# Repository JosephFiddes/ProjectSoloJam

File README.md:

# ProjectSoloJam (Work In Progress)
 Files and info for my solo jam project.

Physical controller to send commands to REAPER, via Open Sound Control. The controller can toggle recording, change track volumes, and set record arming for tracks.

A template REAPER project set up for the controller is found under SoloJamTemplate/SoloJamTemplate.rpp.

## Assembly
Solder the electronic components to the PCB. Note the Arduino UNO is connected via header pins.

Place four of Corner Washer Thing 1 on the piece of wood, and then place the PCB on top, such that the washers are going through the PCB's four corner holes (note: the top-left corner hole is underneath the Arduino UNO - see the image above).

Nail the PCB to the wood piece using nails with a 3mm diameter.

(optional) Place Corner Washer Thing 2 on each of the nails.

## Setup
### Dependencies
Currently, the solution is only designed for Windows.

The following dependencies are required:
 - [oscpp](https://github.com/kaoskorobase/oscpp): library for constructing and parsing OpenSoundControl packets.
 - windows.h

### Compilation

#### Serial2OSC

Prior to compilation, make sure that the port being used by the Arduino matches to port used by Serial2OSC. This can be done by opening serial2osc.cpp, finding the line `#define SERIAL_PORT "COM7"` and changing the `"COM7"` to whatever port the Arduino is using.

This project makes use of the winsock2.h library, and is compiled with MinGW (`g++`). Run `build` to compile the program.

#### Controller
The code for the controller is run on an Arduino UNO, and can be compiled in the Arduino IDE. The electrical circuit diagram of the controller is shown below:

A higher quality version of the image above may be found by [clicking here](./Controller/Controller%20PCB%20Files/Controller%20Schematic.pdf).

### Required REAPER Settings
REAPER needs to have OSC control enabled. 

1. Go to Preferences -> Control/OSC/Web. 
2. Add "OSC (Open Sound Control)" Control surface, with mode "Local port"
3. Set Local listen port to `2345`.

## Operation

With REAPER open, run serial2osc.exe. Pressing a button activates record arm for the corresponding track, and deactivates the record arm for the previous track.

## Bill of Materials

| Product | Qty  |
| ------- | ---: |
| **Electronic Components:** |   |
| FSM103 12x12mm switch  | 16 |
| AKTSC22K switch covers | 16 |
| Arduino Uno            | 1 |
| PTA4553-2010CIB103 Slide Potentiometer | 8 |
| CD4053B Multiplexers | 8 |
| 1 uF Capacitors | 16 |
| 100 Ohm Resistors | 16 |
| 10K Ohm Resistors | 24 |
| 8-long row of Header Pins | 3 |
| 6-long row of Header Pins | 1 |
| Solo Jam Controller PCB | 1 |
| Piece of wood big enough to nail the PCB to | 1 |
| 3mm diameter nails | 4 |
| **3D Printed Files:** |   |
| Corner Washer Thing 1 | 4 |
| Corner Washer Thing 2 | 4 |
| SliderKnob | 8 |

## TODO
 - Features to add to controller:
   - move playhead to start
   - Remove items from particular track
   - Edit tempo?
 - When recording starts while playback is off, playback turns on automatically - but the controller does not update bIsRecording. Also consider when playback turns off while recording, which leads to a wierd state.
 - Figure out bug where random nonsense sometimes gets sent through COM port on start-up. (low priority - hasn't happened in a while, and not a massive concern anyway)
 - In OSCconnection.h, find a way to force "buffer" to be aligned to 32 bits. (Note that the solution is to have it be the first thing in the class definition, but a better solution might be worthwhile since the current one doesn't feel super robust.)
 - Design and manufacture top-piece for controller for stability and isolation of electronics.

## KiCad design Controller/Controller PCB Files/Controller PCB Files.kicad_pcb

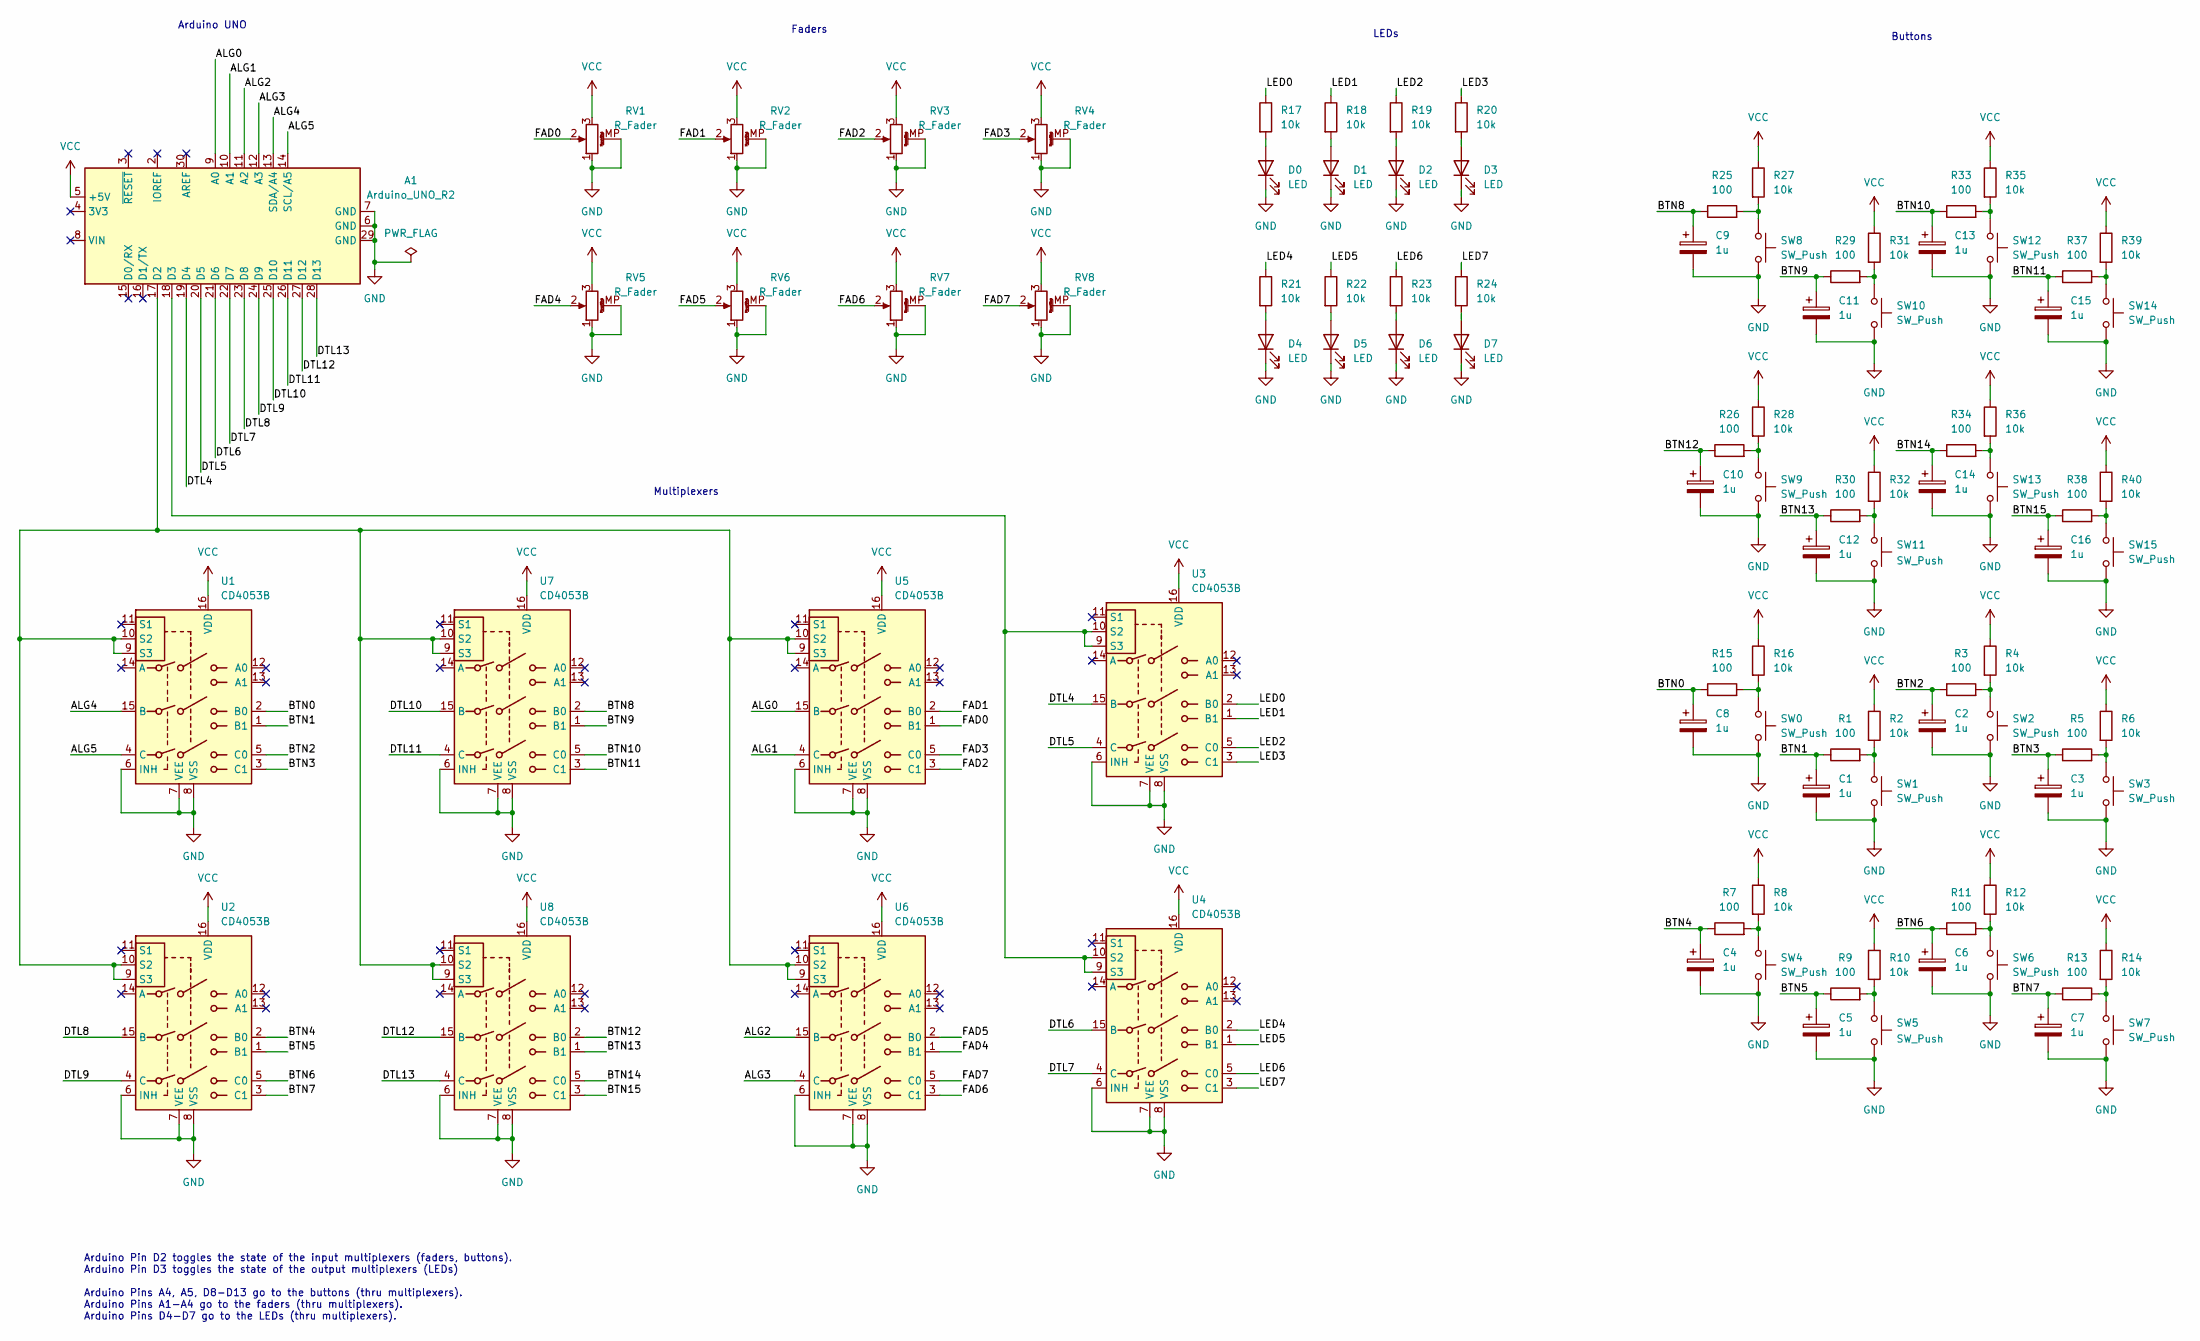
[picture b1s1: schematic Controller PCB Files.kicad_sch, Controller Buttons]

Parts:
A1: Arduino_UNO_R2; Arduino_UNO_R2_WithMountingHoles
C1, C2, C3, C4, C5, C6, C7, C8, C9, C10, C11, C12, C13, C14, C15, C16: 1u; CP_Radial_D5.0mm_P2.50mm
D0, D1, D2, D3, D4, D5, D6, D7: LED; LED_D4.0mm
R1, R3, R5, R7, R9, R11, R13, R15, R25, R26, R29, R30, R33, R34, R37, R38: 100; R_Axial_DIN0207_L6.3mm_D2.5mm_P7.62mm_Horizontal
R2, R4, R6, R8, R10, R12, R14, R16, R17, R18, R19, R20, R21, R22, R23, R24, R27, R28, R31, R32, R35, R36, R39, R40: 10k; R_Axial_DIN0207_L6.3mm_D2.5mm_P7.62mm_Horizontal
RV1, RV2, RV3, RV4, RV5, RV6, RV7, RV8: R_Fader; Potentiometer_Bourns_PTA4543_Single_Slide
SW0, SW1, SW2, SW3, SW4, SW5, SW6, SW7, SW8, SW9, SW10, SW11, SW12, SW13, SW14, SW15: SW_Push; SW_PUSH-12mm
U1, U2, U3, U4, U5, U6, U7, U8: CD4053B; DIP-16_W7.62mm

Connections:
/ALG0: A1.9 (A0), U5.15 (B)
/ALG1: A1.10 (A1), U5.4 (C)
/ALG2: A1.11 (A2), U6.15 (B)
/ALG3: A1.12 (A3), U6.4 (C)
/ALG4: A1.13 (SDA/A4), U1.15 (B)
/ALG5: A1.14 (SCL/A5), U1.4 (C)
/BTN0: C8.1, R15.1, U1.2 (B0)
/BTN1: C1.1, R1.1, U1.1 (B1)
/BTN2: C2.1, R3.1, U1.5 (C0)
/BTN3: C3.1, R5.1, U1.3 (C1)
/BTN4: C4.1, R7.1, U2.2 (B0)
/BTN5: C5.1, R9.1, U2.1 (B1)
/BTN6: C6.1, R11.1, U2.5 (C0)
/BTN7: C7.1, R13.1, U2.3 (C1)
/BTN8: C9.1, R25.1, U7.2 (B0)
/BTN9: C11.1, R29.1, U7.1 (B1)
/BTN10: C13.1, R33.1, U7.5 (C0)
/BTN11: C15.1, R37.1, U7.3 (C1)
/BTN12: C10.1, R26.1, U8.2 (B0)
/BTN13: C12.1, R30.1, U8.1 (B1)
/BTN14: C14.1, R34.1, U8.5 (C0)
/BTN15: C16.1, R38.1, U8.3 (C1)
/DTL4: A1.19 (D4), U3.15 (B)
/DTL5: A1.20 (D5), U3.4 (C)
/DTL6: A1.21 (D6), U4.15 (B)
/DTL7: A1.22 (D7), U4.4 (C)
/DTL8: A1.23 (D8), U2.15 (B)
/DTL9: A1.24 (D9), U2.4 (C)
/DTL10: A1.25 (D10), U7.15 (B)
/DTL11: A1.26 (D11), U7.4 (C)
/DTL12: A1.27 (D12), U8.15 (B)
/DTL13: A1.28 (D13), U8.4 (C)
/FAD0: RV1.2, U5.1 (B1)
/FAD1: RV2.2, U5.2 (B0)
/FAD2: RV3.2, U5.3 (C1)
/FAD3: RV4.2, U5.5 (C0)
/FAD4: RV5.2, U6.1 (B1)
/FAD5: RV6.2, U6.2 (B0)
/FAD6: RV7.2, U6.3 (C1)
/FAD7: RV8.2, U6.5 (C0)
/LED0: R17.1, U3.2 (B0)
/LED1: R18.1, U3.1 (B1)
/LED2: R19.1, U3.5 (C0)
/LED3: R20.1, U3.3 (C1)
/LED4: R21.1, U4.2 (B0)
/LED5: R22.1, U4.1 (B1)
/LED6: R23.1, U4.5 (C0)
/LED7: R24.1, U4.3 (C1)
GND: A1.6 (GND), A1.7 (GND), A1.29 (GND), C1.2, C2.2, C3.2, C4.2, C5.2, C6.2, C7.2, C8.2, C9.2, C10.2, C11.2, C12.2, C13.2, C14.2, C15.2, C16.2, D0.1 (K), D1.1 (K), D2.1 (K), D3.1 (K), D4.1 (K), D5.1 (K), D6.1 (K), D7.1 (K), RV1.1, RV1.MP (MountPin), RV2.1, RV2.MP (MountPin), RV3.1, RV3.MP (MountPin), RV4.1, RV4.MP (MountPin), RV5.1, RV5.MP (MountPin), RV6.1, RV6.MP (MountPin), RV7.1, RV7.MP (MountPin), RV8.1, RV8.MP (MountPin), SW0.2, SW1.2, SW2.2, SW3.2, SW4.2, SW5.2, SW6.2, SW7.2, SW8.2, SW9.2, SW10.2, SW11.2, SW12.2, SW13.2, SW14.2, SW15.2, U1.6 (INH), U1.7 (VEE), U1.8 (VSS), U2.6 (INH), U2.7 (VEE), U2.8 (VSS), U3.6 (INH), U3.7 (VEE), U3.8 (VSS), U4.6 (INH), U4.7 (VEE), U4.8 (VSS), U5.6 (INH), U5.7 (VEE), U5.8 (VSS), U6.6 (INH), U6.7 (VEE), U6.8 (VSS), U7.6 (INH), U7.7 (VEE), U7.8 (VSS), U8.6 (INH), U8.7 (VEE), U8.8 (VSS)
unnamed: A1.17 (D2), U1.9 (S3), U1.10 (S2), U2.9 (S3), U2.10 (S2), U5.9 (S3), U5.10 (S2), U6.9 (S3), U6.10 (S2), U7.9 (S3), U7.10 (S2), U8.9 (S3), U8.10 (S2)
unnamed: A1.18 (D3), U3.9 (S3), U3.10 (S2), U4.9 (S3), U4.10 (S2)
unnamed: D0.2 (A), R17.2
unnamed: D1.2 (A), R18.2
unnamed: D2.2 (A), R19.2
unnamed: D3.2 (A), R20.2
unnamed: D4.2 (A), R21.2
unnamed: D5.2 (A), R22.2
unnamed: D6.2 (A), R23.2
unnamed: D7.2 (A), R24.2
unnamed: R1.2, R2.2, SW1.1
unnamed: R3.2, R4.2, SW2.1
unnamed: R5.2, R6.2, SW3.1
unnamed: R7.2, R8.2, SW4.1
unnamed: R9.2, R10.2, SW5.1
unnamed: R11.2, R12.2, SW6.1
unnamed: R13.2, R14.2, SW7.1
unnamed: R15.2, R16.2, SW0.1
unnamed: R25.2, R27.2, SW8.1
unnamed: R26.2, R28.2, SW9.1
unnamed: R29.2, R31.2, SW10.1
unnamed: R30.2, R32.2, SW11.1
unnamed: R33.2, R35.2, SW12.1
unnamed: R34.2, R36.2, SW13.1
unnamed: R37.2, R39.2, SW14.1
unnamed: R38.2, R40.2, SW15.1
VCC: A1.5 (+5V), R2.1, R4.1, R6.1, R8.1, R10.1, R12.1, R14.1, R16.1, R27.1, R28.1, R31.1, R32.1, R35.1, R36.1, R39.1, R40.1, RV1.3, RV2.3, RV3.3, RV4.3, RV5.3, RV6.3, RV7.3, RV8.3, U1.16 (VDD), U2.16 (VDD), U3.16 (VDD), U4.16 (VDD), U5.16 (VDD), U6.16 (VDD), U7.16 (VDD), U8.16 (VDD)

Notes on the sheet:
Buttons
LEDs
Arduino Pin D2 toggles the state of the input multiplexers (faders, buttons). Arduino Pin D3 toggles the state of the output multiplexers (LEDs) Arduino Pins A4, A5, D8-D13 go to the buttons (thru multiplexers). Arduino Pins A1-A4 go to the faders (thru multiplexers). Arduino Pins D4-D7 go to the L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
Multiplexers
Arduino UNO
Faders

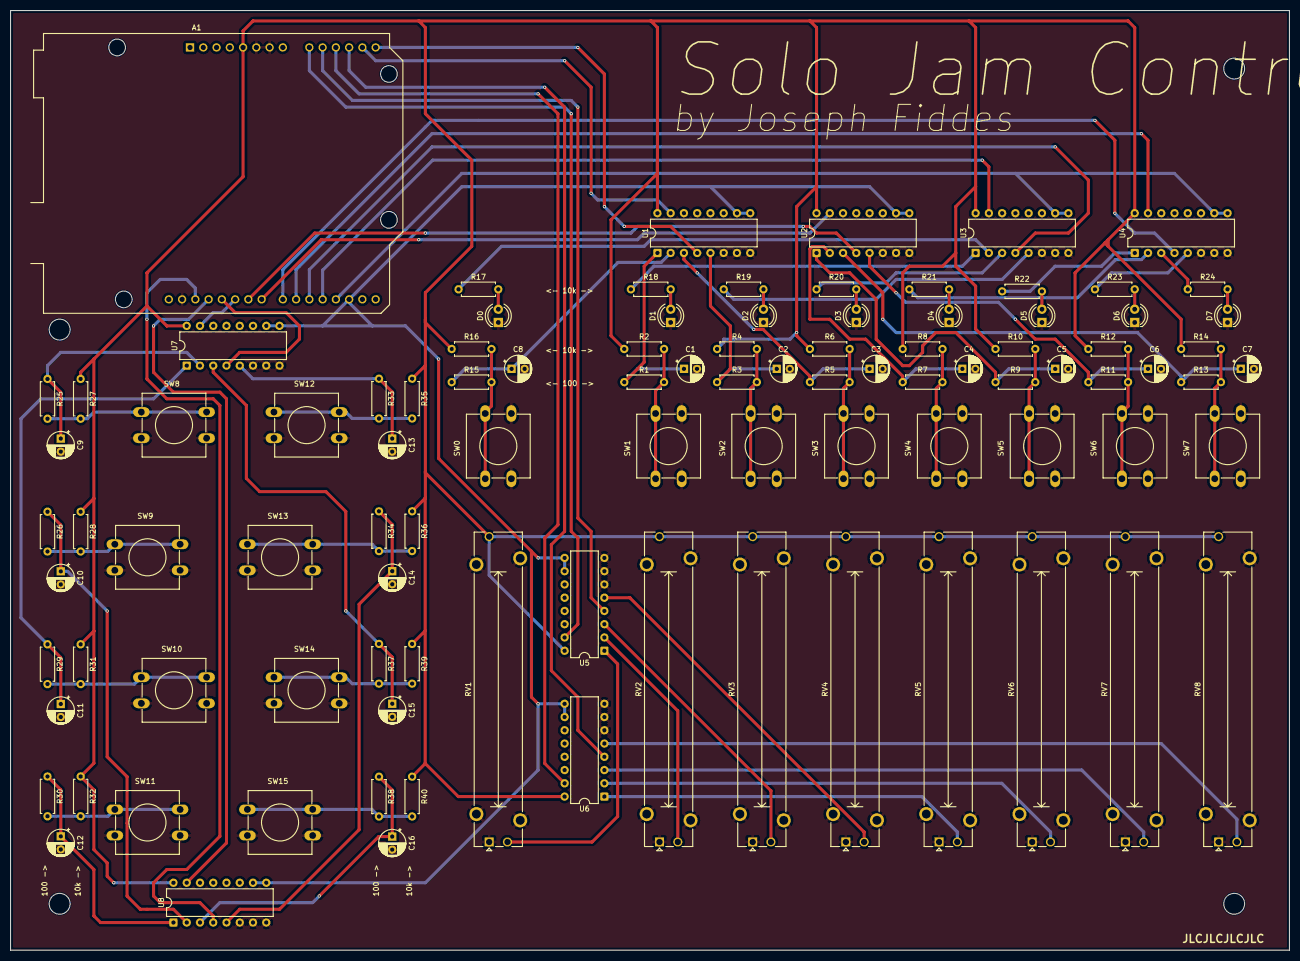
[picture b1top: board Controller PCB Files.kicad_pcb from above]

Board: 4 copper layers, 245.0 x 180.0 mm, 97 parts (0 on the bottom side), 76 nets.

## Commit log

2024-11-26 Predefined OSC messages successfully sent to REAPER.
2024-12-02 Toggle buttons implemented for hardware controller
2024-12-02 Update README for controller
2024-12-04 Radio-style buttons and serial write implemented
2024-12-10 Radio buttons successfully control REAPER.
2024-12-10 Adjust TODO list
2024-12-11 Refactored code to better encapsulate Toggle_buttons operation.
2024-12-12 Added support for OSC "toggle" commands, and added button for toggling recording.
2024-12-12 Update TODO list
2025-02-07 Added more detail to README and moved REAPER to version 7
2025-03-28 Added support for sliders, and increased number of buttons
2025-03-28 Added Base plate, updated BOM
2025-05-04 Prepare for publication (note project is still unfinished)
2025-05-07 Track 1 now used as master track; ReaStream now reacts to master fader
2025-05-14 Allows choice of toggle on button up or button down. Defaults to button down
2025-05-14 Changing record arm stops recording
2025-05-16 Items now overdub, rather than create new take.
2025-06-25 Added more compression and limiter to Reaper template
2025-07-29 Makes chosen Serial port more customisable (changed to COM7)
2025-07-29 Adjust metronome
2025-08-09 Added controller PCB files and updated README with new controller schematic
2025-08-09 Update BoM and TODO list
2025-08-14 Fix tracks 6,7,8 recording mono (rather than stereo)
2025-08-20 Move controller logic to serial2osc. SLIDERS YET TO BE UPDATED
2025-08-20 Added sliders to refactor
2025-08-25 Updated controller to match with circuit board.
2025-08-25 Fixed bug where command would be resent multiple times
2025-09-01 PCB update. Added washer STLs and updated BoM & header image
2025-09-01 Added play and metronome toggles.
2025-09-10 Changed ReaStream identifier to hopefully reduce clicks
    Following the advice given in this reddit comment:
    https://www.reddit.com/r/Reaper/comments/fxn49j/comment/hvx199t
2025-11-20 Change recording tracks to mono (new interface is mono)
2025-11-26 Removed record-arm of first track (added accidentally in prev. commit)
2026-02-05 Added delete all items button, default arguments for add_to_buffer, and batch file for compilation
2026-02-26 Added names to tracks
2026-03-03 Better control over volume
2026-03-03 Added delay to microcontroller so serial2osc isn't stuck waiting for a bunch of similar commands
